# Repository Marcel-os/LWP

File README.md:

# Linefollower
Pliki związane z budową robota LF

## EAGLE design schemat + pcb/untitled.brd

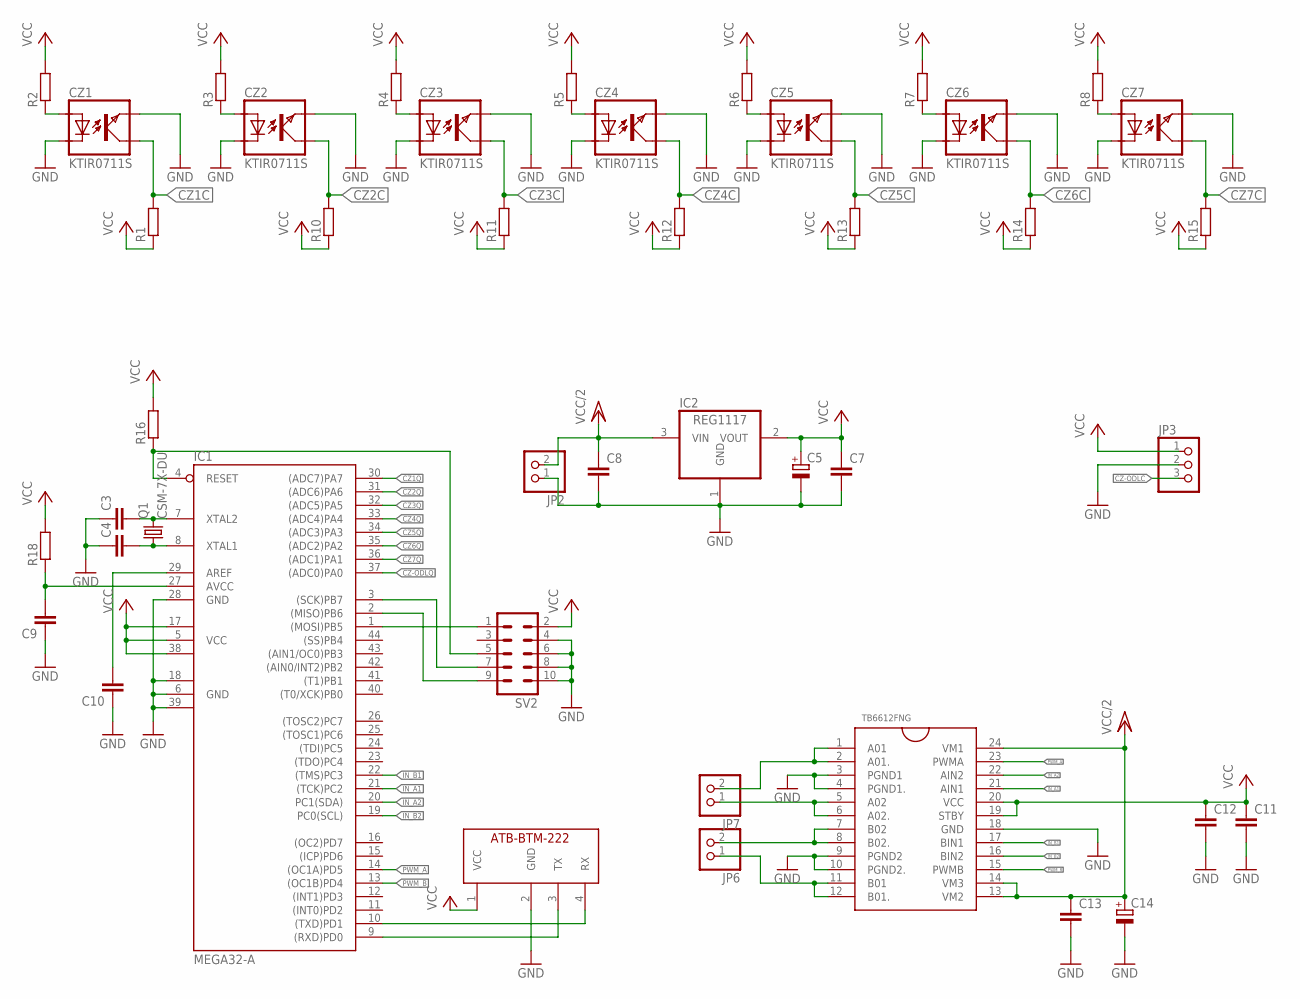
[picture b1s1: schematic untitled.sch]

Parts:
C3, C4, C7, C8, C9, C10, C11, C12, C13: C-EUC1206K; C1206K
C5, C14: CPOL-EU175TMP-0810; 175TMP-0810
CZ1, CZ2, CZ3, CZ4, CZ5, CZ6, CZ7: KTIR0711S; TOP
IC1: MEGA32-A; TQFP44
IC2: REG1117; SOT223
JP2, JP6, JP7: PINHD-1X2; 1X02
JP3: PINHD-1X3; 1X03
Q1: CSM-7X-DU
R1, R2, R3, R4, R5, R6, R7, R8, R10, R11, R12, R13, R14, R15, R16, R18: R-EU_R0603; R0603
SV2: MA05-2
U$1: TB6612FNG; SSOP24
U$2: ATB-BTM-222

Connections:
CZ1C: CZ1.KOLEKTOR, R1.2
CZ1Q: IC1.30 ((ADC7)PA7)
CZ2C: CZ2.KOLEKTOR, R10.2
CZ2Q: IC1.31 ((ADC6)PA6)
CZ3C: CZ3.KOLEKTOR, R11.2
CZ3Q: IC1.32 ((ADC5)PA5)
CZ4C: CZ4.KOLEKTOR, R12.2
CZ4Q: IC1.33 ((ADC4)PA4)
CZ5C: CZ5.KOLEKTOR, R13.2
CZ5Q: IC1.34 ((ADC3)PA3)
CZ6C: CZ6.KOLEKTOR, R14.2
CZ6Q: IC1.35 ((ADC2)PA2)
CZ7C: CZ7.KOLEKTOR, R15.2
CZ7Q: IC1.36 ((ADC1)PA1)
CZ-ODLC: JP3.3
CZ-ODLQ: IC1.37 ((ADC0)PA0)
GND: C3.1, C4.1, C5.-, C7.2, C8.2, C9.1, C10.1, C11.2, C12.2, C13.2, C14.-, CZ1.EMITER, CZ1.KATODA, CZ2.EMITER, CZ2.KATODA, CZ3.EMITER, CZ3.KATODA, CZ4.EMITER, CZ4.KATODA, CZ5.EMITER, CZ5.KATODA, CZ6.EMITER, CZ6.KATODA, CZ7.EMITER, CZ7.KATODA, IC1.6 (GND), IC1.18 (GND1), IC1.28 (GND), IC1.39 (GND2), IC2.1 (GND), JP2.1, JP3.2, SV2.4, SV2.6, SV2.8, SV2.10, U$1.3 (PGND1), U$1.4 (PGND1.), U$1.9 (PGND2), U$1.10 (PGND2.), U$1.18 (GND), U$2.2 (GND)
IN_A1: IC1.21 ((TCK)PC2), U$1.21 (AIN1)
IN_A2: IC1.20 (PC1(SDA)), U$1.22 (AIN2)
IN_B1: IC1.22 ((TMS)PC3), U$1.17 (BIN1)
IN_B2: IC1.19 (PC0(SCL)), U$1.16 (BIN2)
unnamed: IC1.10 ((TXD)PD1), U$2.4 (RX)
unnamed: IC1.9 ((RXD)PD0), U$2.3 (TX)
unnamed: C9.2, IC1.27 (AVCC), R18.1
unnamed: C10.2, IC1.29 (AREF)
unnamed: IC1.1 ((MOSI)PB5), SV2.1
unnamed: IC1.3 ((SCK)PB7), SV2.7
unnamed: IC1.2 ((MISO)PB6), SV2.9
unnamed: IC1.4 (RESET), R16.1, SV2.5
unnamed: C3.2, IC1.7 (XTAL2), Q1.2
unnamed: C4.2, IC1.8 (XTAL1), Q1.1
unnamed: CZ1.ANODA, R2.1
unnamed: CZ2.ANODA, R3.1
unnamed: JP6.2, U$1.7 (B02), U$1.8 (B02.)
unnamed: JP6.1, U$1.11 (B01), U$1.12 (B01.)
unnamed: JP7.1, U$1.5 (A02), U$1.6 (A02.)
unnamed: JP7.2, U$1.1 (A01), U$1.2 (A01.)
unnamed: CZ3.ANODA, R4.1
unnamed: CZ4.ANODA, R5.1
unnamed: CZ5.ANODA, R6.1
unnamed: CZ6.ANODA, R7.1
unnamed: CZ7.ANODA, R8.1
PWM_A: IC1.14 ((OC1A)PD5), U$1.23 (PWMA)
PWM_B: IC1.13 ((OC1B)PD4), U$1.15 (PWMB)
VCC: C5.+, C7.1, C11.1, C12.1, IC1.5 (VCC), IC1.17 (VCC1), IC1.38 (VCC2), IC2.2 (VOUT), JP3.1, R1.1, R2.2, R3.2, R4.2, R5.2, R6.2, R7.2, R8.2, R10.1, R11.1, R12.1, R13.1, R14.1, R15.1, R16.2, R18.2, SV2.2, U$1.19 (STBY), U$1.20 (VCC), U$2.1 (VCC)
VCC/2: C8.1, C13.1, C14.+, IC2.3 (VIN), JP2.2, U$1.13 (VM2), U$1.14 (VM3), U$1.24 (VM1)

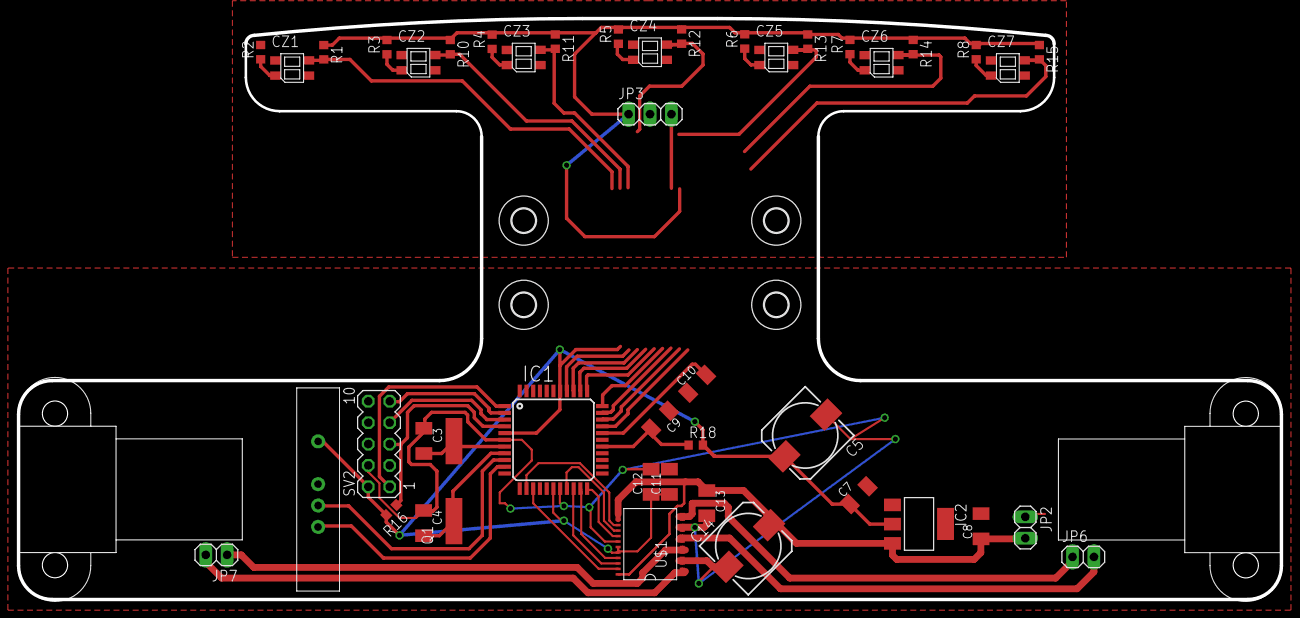
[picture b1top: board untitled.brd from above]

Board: 2 copper layers, 150.0 x 69.0 mm, 50 parts (0 on the bottom side), 37 nets.

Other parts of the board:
U$3, U$6, U$7, U$8: 2,8
U$4, U$5: HP_NM

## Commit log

2020-04-21 Initial comit
2020-04-21 Dodano schemat oraz pcb płytki robota
2020-04-21 dodano zdjęcia konstrukcji
2020-04-21 zmiana nazwy
2020-04-23 Dodanie modelu kola
2020-04-23 Dodanie modelu lacznika
2020-04-23 Dodanie modelu uchwytu silnika
2020-04-23 Dodanie modeli solidworks
2020-06-14 Dodano regulator PD jazdy po lini
2020-06-14 Dodano prosty algorytm podążania za ścieżką
2020-06-14 Dodano prosty algorytm omijania przeszkód
2020-06-15 Prędkość maksymalna na poziomie 1m/sek
2020-06-15 Dodano poszukiwanie lini po wyjechaniu poza nią
2020-06-16 Uporzadkowanie kodu programu
